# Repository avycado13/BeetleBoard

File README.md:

# BeetleBoard

Ever wanted to build a beetleweight but didn't want the huge mess of wires? No? Too bad. Meet BeetleBoard.
A perfect board for controlling your beetleweight battlebot using an ESP32.

## Features:
- 8 ports for ESCs
- 8 motor power ports
- Optional ExpressLRS Receiver
- 6 axis IMU with handling for up to 320Gs
- Software controllable battery undervoltage lockout circuitry
- Battery voltage sensing
- Powered by a XIAO ESP32-C6
- Ability to add a power switch (preferably fingertech)

## Why?
I built this because I saw battlebots at open sauce and thought "I want to make one of those". While looking through things about beetleweights and especially the ones with custom PCBs, I found out that most of the PCBs I found were specifically meant for one design and couldn't really be used for any type of bot. Coincidentally, My friend was trying to run a battlebots elective at our school and would need a control system to test before teaching the students.

## Bill of Materials (BOM)
**REVIEWERS PLEASE USE CSV**
This is just a rough list compiled from my schematic. The actual one is [here](./BOM.csv)

| Qty | Reference | Value | Package | Description |
|----:|-----------|-------|---------|-------------|
| 1 | U1 | XIAO ESP32-C6 SMD | XIAO | Seeed Studio XIAO ESP32-C6 module (main MCU) |
| 1 | U2 | TPS563200 | SOT-23-6 | 3A synchronous step-down buck converter (5V rail) |
| 1 | U3 | LSM6DSV320XTR | LGA-14 | 6-axis IMU, up to 320G |
| 1 | L1 | 4.7µH | 1210 | Buck converter power inductor |
| 5 | C1, C2, C3, C6, C8 | 22µF | 0805 | Bulk decoupling / output capacitance |
| 5 | C4, C5, C7, C9, C10 | 100nF | 0805 | Decoupling capacitors |
| 9 | R1-R6, R11-R13 | 33kΩ | 0805 | Resistor |
| 1 | R7 | 56kΩ | 0805 | Resistor |
| 1 | R8 | 10kΩ | 0805 | Resistor |
| 1 | R9 | 33.2kΩ | 0805 | Resistor |
| 1 | R10 | 120kΩ | 0805 | Resistor |
| 1 | R14 | 100kΩ | 0805 | Resistor |
| 1 | D1 | SMAJ40CA | SMA | 40V TVS diode (battery reverse/over-voltage protection) |
| 8 | D2-D9 | PESD5V0V1BA | SOD-323 | 5V ESD protection diodes |
| 1 | J1 | AMASS XT60-F | XT60 | Battery connector |
| 8 | J2-J7, J16, J17 | ESC signal port | 1×3 pin header 2.54mm | ESC signal power ports A-H |
| 8 | J8-J15 | VBAT ESC port | Solder wire 2-pin | Motor power ports |
| 1 | J18 | ELRS Receiver | BetaFPV Lite | Optional ExpressLRS receiver socket |
| 1 | SW1 | FingerTech Switch | Solder wire 2-pin | External power switch connection |
| 5 | TP1-TP5 | Test point | 3mm pad | Test/debug points (VBAT, 5V, GND, 3.3V, VBUS) |

# Firmware
At the moment, the firmware in the folder is some test code I had AI write. I will most definitely rewrite all the code when I have an actual board to test it on.

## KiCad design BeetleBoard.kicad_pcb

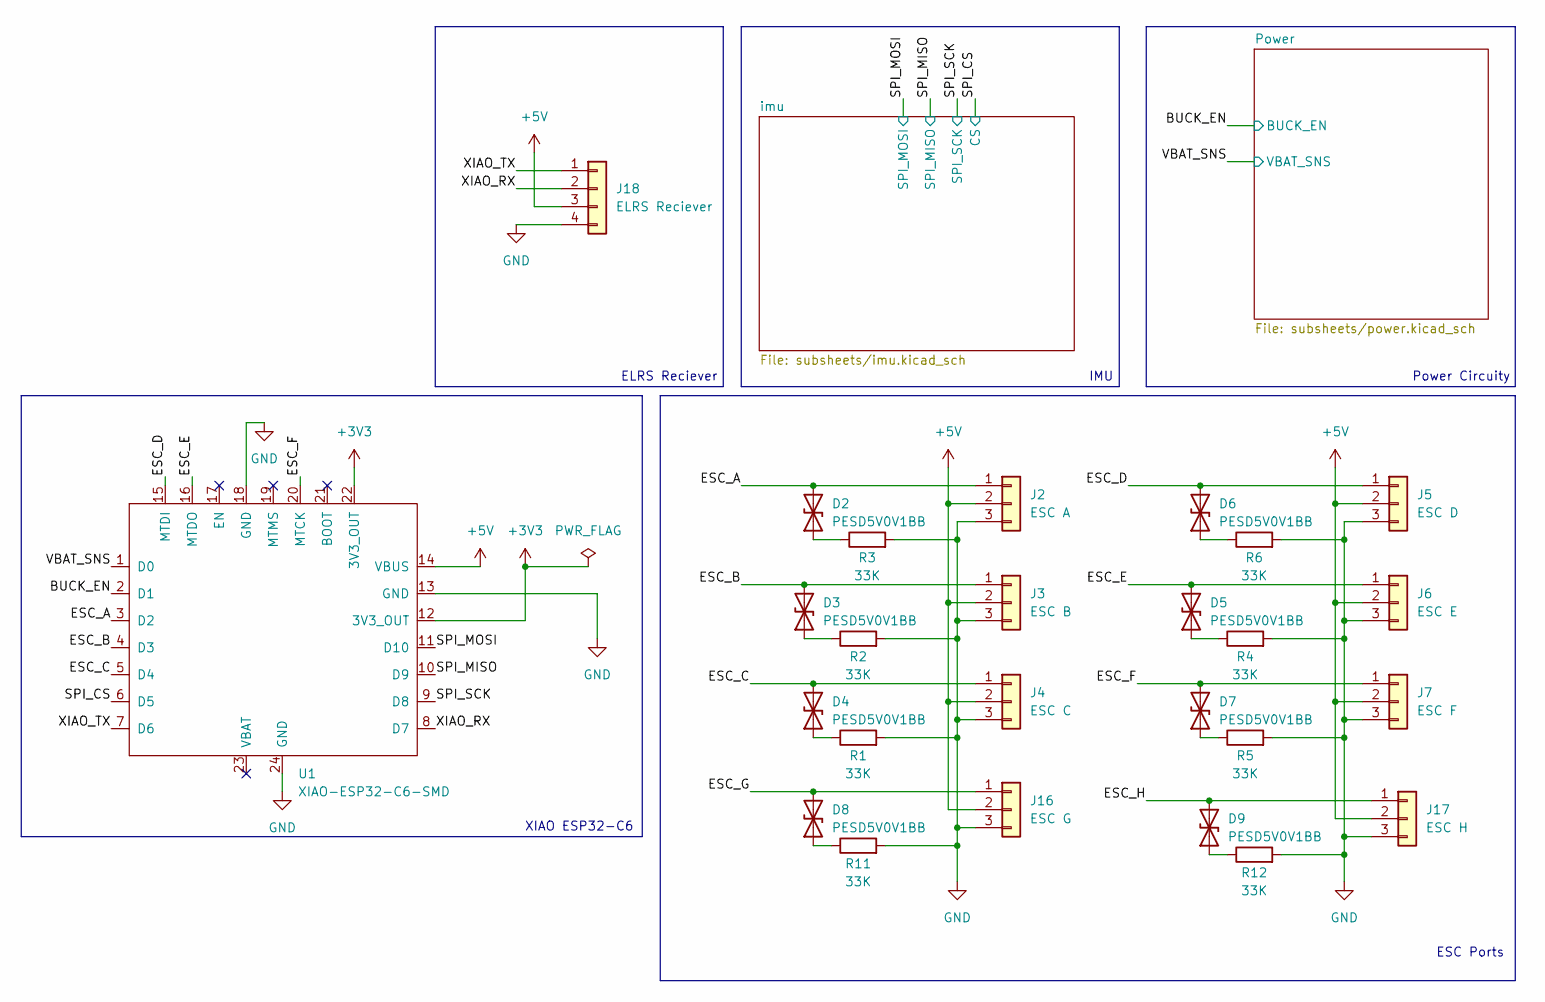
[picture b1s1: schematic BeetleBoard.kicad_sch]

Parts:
D2, D3, D4, D5, D6, D7, D8, D9: PESD5V0V1BB; D_SOD-323
J2: ESC A; PinHeader_1x03_P2.54mm_Vertical
J3: ESC B; PinHeader_1x03_P2.54mm_Vertical
J4: ESC C; PinHeader_1x03_P2.54mm_Vertical
J5: ESC D; PinHeader_1x03_P2.54mm_Vertical
J6: ESC E; PinHeader_1x03_P2.54mm_Vertical
J7: ESC F; PinHeader_1x03_P2.54mm_Vertical
J16: ESC G; PinHeader_1x03_P2.54mm_Vertical
J17: ESC H; PinHeader_1x03_P2.54mm_Vertical
J18: ELRS Reciever; BetaFPV_ELRS_Lite
R1, R2, R3, R4, R5, R6, R11, R12: 33K; R_0805_2012Metric_Pad1.20x1.40mm_HandSolder
U1: XIAO-ESP32-C6-SMD

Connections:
+3V3: U1.12 (3V3_OUT), U1.22 (3V3_OUT); also elsewhere on the board
+5V: J2.2 (+5V), J3.2 (+5V), J4.2 (+5V), J5.2 (+5V), J6.2 (+5V), J7.2 (+5V), J16.2 (+5V), J17.2 (+5V), J18.3, U1.14 (VBUS); also elsewhere on the board
/BUCK_EN: U1.2 (D1); also elsewhere on the board
/ESC_A: D2.2 (A2), J2.1 (DShot/PWM), U1.3 (D2)
/ESC_B: D3.2 (A2), J3.1 (DShot/PWM), U1.4 (D3)
/ESC_C: D4.2 (A2), J4.1 (DShot/PWM), U1.5 (D4)
/ESC_D: D6.2 (A2), J5.1 (DShot/PWM), U1.15 (MTDI)
/ESC_E: D5.2 (A2), J6.1 (DShot/PWM), U1.16 (MTDO)
/ESC_F: D7.2 (A2), J7.1 (DShot/PWM), U1.20 (MTCK)
/ESC_G: D8.2 (A2), J16.1 (DShot/PWM)
/ESC_H: D9.2 (A2), J17.1 (DShot/PWM)
/SPI_CS: U1.6 (D5); also elsewhere on the board
/SPI_MISO: U1.10 (D9); also elsewhere on the board
/SPI_MOSI: U1.11 (D10); also elsewhere on the board
/SPI_SCK: U1.9 (D8); also elsewhere on the board
/VBAT_SNS: U1.1 (D0); also elsewhere on the board
/XIAO_RX: J18.2, U1.8 (D7)
/XIAO_TX: J18.1, U1.7 (D6)
GND: J2.3 (GND), J3.3 (GND), J4.3 (GND), J5.3 (GND), J6.3 (GND), J7.3 (GND), J16.3 (GND), J17.3 (GND), J18.4, R1.2, R2.2, R3.2, R4.2, R5.2, R6.2, R11.2, R12.2, U1.13 (GND), U1.18 (GND), U1.24 (GND); also elsewhere on the board
unnamed: D2.1 (A1), R3.1
unnamed: D3.1 (A1), R2.1
unnamed: D4.1 (A1), R1.1
unnamed: D5.1 (A1), R4.1
unnamed: D6.1 (A1), R6.1
unnamed: D7.1 (A1), R5.1
unnamed: D8.1 (A1), R11.1
unnamed: D9.1 (A1), R12.1

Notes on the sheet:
Power Circuity
XIAO ESP32-C6
ELRS Reciever
IMU
ESC Ports

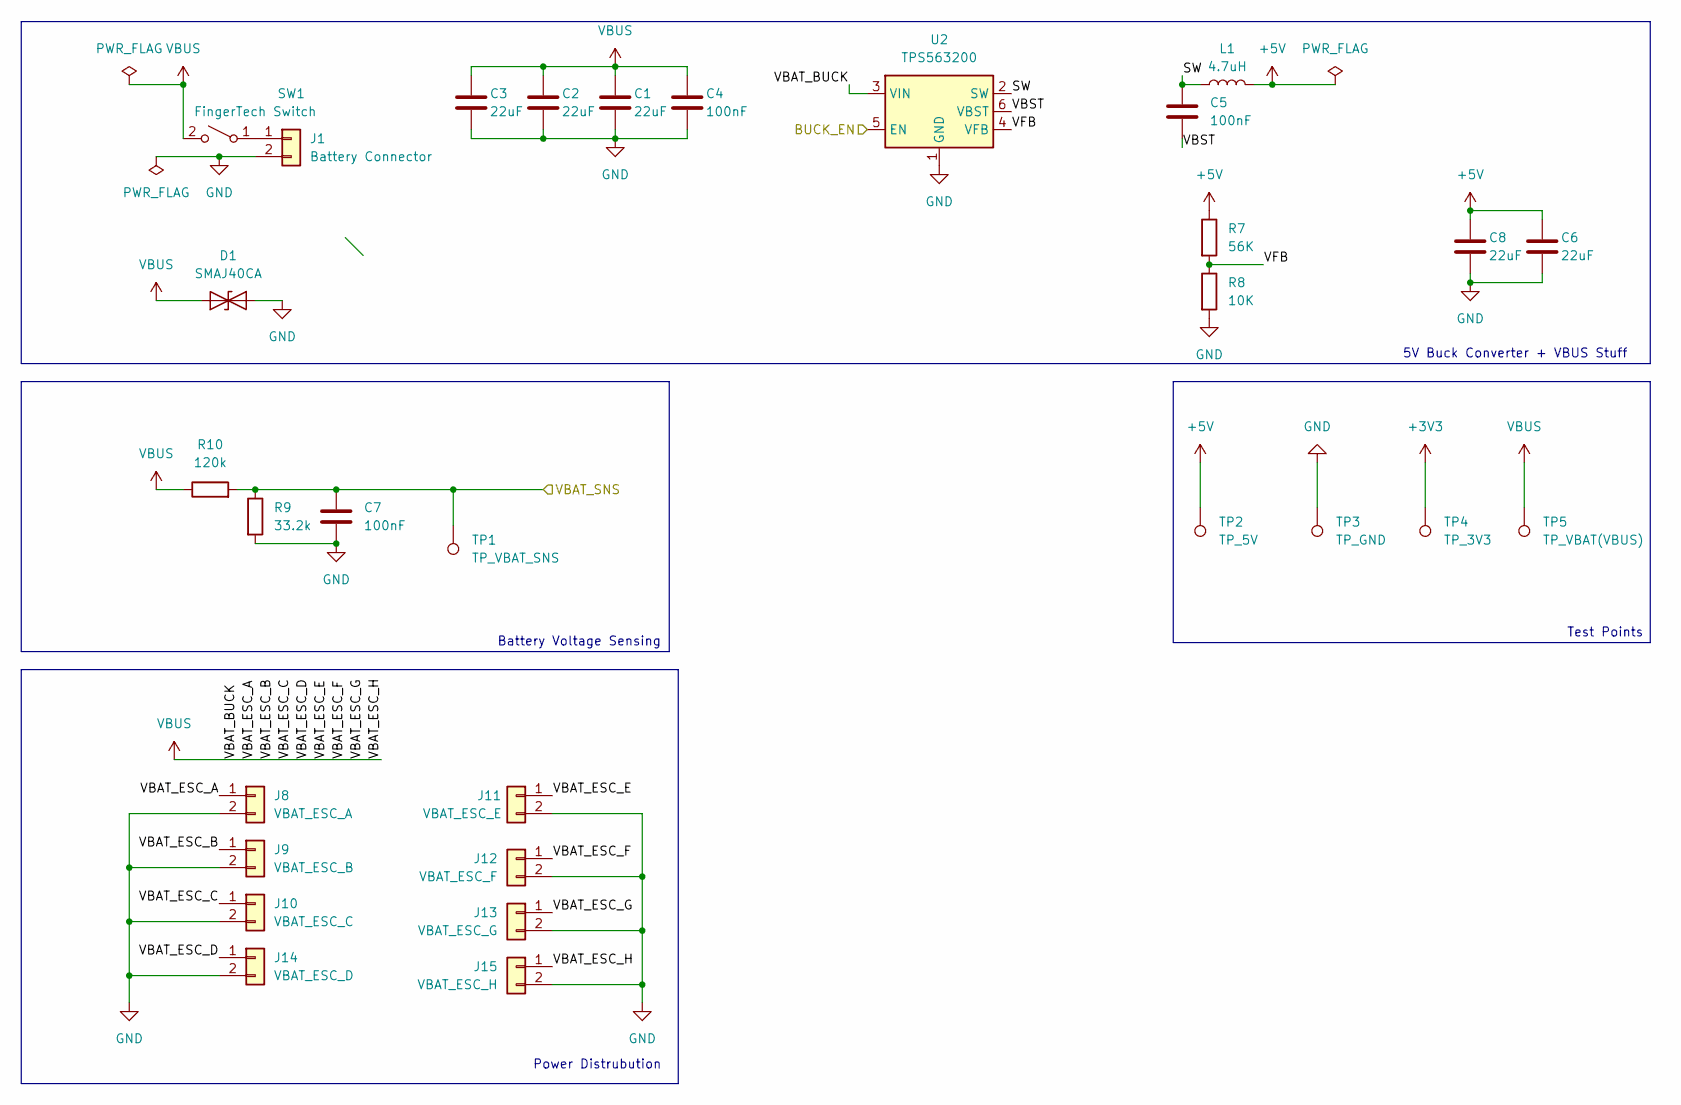
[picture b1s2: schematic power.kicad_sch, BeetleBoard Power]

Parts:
C1, C2, C3, C6, C8: 22uF; C_0805_2012Metric_Pad1.18x1.45mm_HandSolder
C4, C5, C7: 100nF; C_0805_2012Metric_Pad1.18x1.45mm_HandSolder
D1: SMAJ40CA; D_SMA
J1: Battery Connector; AMASS_XT60-F_1x02_P7.20mm_Vertical
J8: VBAT_ESC_A; Power_SolderPad_2Pin_P5.08mm_D2.0mm
J9: VBAT_ESC_B; Power_SolderPad_2Pin_P5.08mm_D2.0mm
J10: VBAT_ESC_C; Power_SolderPad_2Pin_P5.08mm_D2.0mm
J11: VBAT_ESC_E; Power_SolderPad_2Pin_P5.08mm_D2.0mm
J12: VBAT_ESC_F; Power_SolderPad_2Pin_P5.08mm_D2.0mm
J13: VBAT_ESC_G; Power_SolderPad_2Pin_P5.08mm_D2.0mm
J14: VBAT_ESC_D; Power_SolderPad_2Pin_P5.08mm_D2.0mm
J15: VBAT_ESC_H; Power_SolderPad_2Pin_P5.08mm_D2.0mm
L1: 4.7uH; L_1210_3225Metric_Pad1.42x2.65mm_HandSolder
R7: 56K; R_0805_2012Metric_Pad1.20x1.40mm_HandSolder
R8: 10K; R_0805_2012Metric_Pad1.20x1.40mm_HandSolder
R9: 33.2k; R_0805_2012Metric_Pad1.20x1.40mm_HandSolder
R10: 120k; R_0805_2012Metric_Pad1.20x1.40mm_HandSolder
SW1: FingerTech Switch; Power_SolderPad_2Pin_P5.08mm_D2.0mm
TP1: TP_VBAT_SNS; TestPoint_Pad_D3.0mm
TP2: TP_5V; TestPoint_Pad_D3.0mm
TP3: TP_GND; TestPoint_Pad_D3.0mm
TP4: TP_3V3; TestPoint_Pad_D3.0mm
TP5: TP_VBAT(VBUS); TestPoint_Pad_D3.0mm
U2: TPS563200; SOT-23-6

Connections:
+3V3: TP4.1 (1_1); also elsewhere on the board
+5V: C6.1, C8.1, L1.2, R7.1, TP2.1 (1_1); also elsewhere on the board
/BUCK_EN: U2.5 (EN); also elsewhere on the board
/Power/SW: C5.1, L1.1, U2.2 (SW)
/Power/VBST: C5.2, U2.6 (VBST)
/Power/VFB: R7.2, R8.1, U2.4 (VFB)
/VBAT_SNS: C7.1, R9.1, R10.2, TP1.1 (1_1); also elsewhere on the board
GND: C1.2, C2.2, C3.2, C4.2, C6.2, C7.2, C8.2, D1.2 (A2), J1.2, J8.2, J9.2, J10.2, J11.2, J12.2, J13.2, J14.2, J15.2, R8.2, R9.2, TP3.1 (1_1), U2.1 (GND); also elsewhere on the board
unnamed: J1.1, SW1.1 (A)
VBUS: C1.1, C2.1, C3.1, C4.1, D1.1 (A1), J8.1, J9.1, J10.1, J11.1, J12.1, J13.1, J14.1, J15.1, R10.1, SW1.2 (B), TP5.1 (1_1), U2.3 (VIN)

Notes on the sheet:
Battery Voltage Sensing
5V Buck Converter + VBUS Stuff
Test Points
Power Distrubution

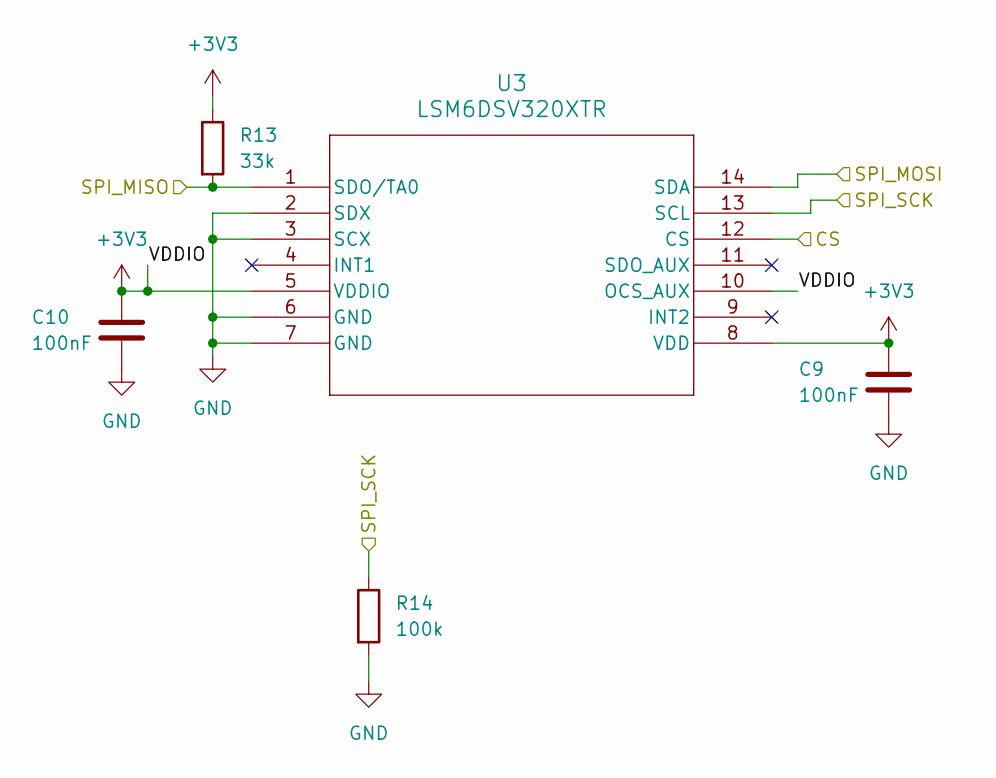
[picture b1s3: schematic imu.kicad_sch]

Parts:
C9, C10: 100nF; C_0805_2012Metric_Pad1.18x1.45mm_HandSolder
R13: 33k; R_0805_2012Metric_Pad1.20x1.40mm_HandSolder
R14: 100k; R_0805_2012Metric_Pad1.20x1.40mm_HandSolder
U3: LSM6DSV320XTR; LGA-14L_2p5X3X0p83_STM

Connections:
+3V3: C9.1, C10.1, R13.1, U3.5 (VDDIO), U3.8 (VDD), U3.10 (OCS_AUX); also elsewhere on the board
/SPI_CS: U3.12 (CS); also elsewhere on the board
/SPI_MISO: R13.2, U3.1 (SDO/TA0); also elsewhere on the board
/SPI_MOSI: U3.14 (SDA); also elsewhere on the board
/SPI_SCK: R14.1, U3.13 (SCL); also elsewhere on the board
GND: C9.2, C10.2, R14.2, U3.2 (SDX), U3.3 (SCX), U3.6 (GND), U3.7 (GND); also elsewhere on the board

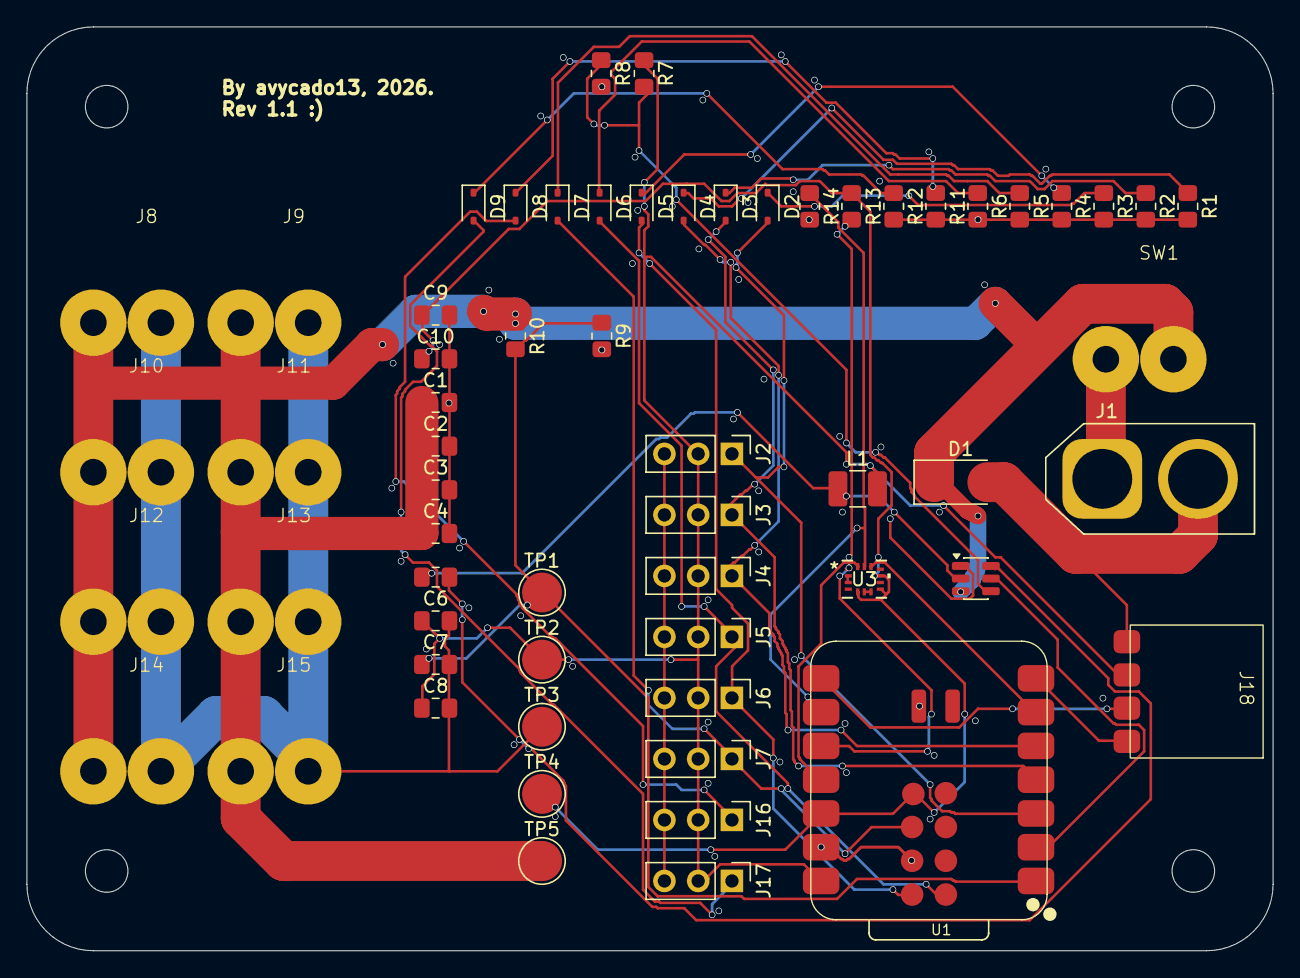
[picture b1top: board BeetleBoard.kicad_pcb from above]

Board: 2 copper layers, 93.8 x 69.5 mm, 61 parts (0 on the bottom side), 32 nets.

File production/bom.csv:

Designator,Footprint,Quantity,Value,LCSC Part #
"C1, C2, C3, C6, C8",0805,5,22uF,
"C10, C4, C5, C7, C9",0805,5,100nF,
D1,D_SMA,1,SMAJ40CA,
"D2, D3, D4, D5, D6, D7, D8, D9",D_SOD-323,8,PESD5V0V1BB,
J1,AMASS_XT60-F_1x02_P7.20mm_Vertical,1,Battery Connector,
J10,Power_SolderPad_2Pin_P5.08mm_D2.0mm,1,VBAT_ESC_C,
J11,Power_SolderPad_2Pin_P5.08mm_D2.0mm,1,VBAT_ESC_E,
J12,Power_SolderPad_2Pin_P5.08mm_D2.0mm,1,VBAT_ESC_F,
J13,Power_SolderPad_2Pin_P5.08mm_D2.0mm,1,VBAT_ESC_G,
J14,Power_SolderPad_2Pin_P5.08mm_D2.0mm,1,VBAT_ESC_D,
J15,Power_SolderPad_2Pin_P5.08mm_D2.0mm,1,VBAT_ESC_H,
J16,PinHeader_1x03_P2.54mm_Vertical,1,ESC G,
J17,PinHeader_1x03_P2.54mm_Vertical,1,ESC H,
J18,BetaFPV_ELRS_Lite,1,ELRS Reciever,
J2,PinHeader_1x03_P2.54mm_Vertical,1,ESC A,
J3,PinHeader_1x03_P2.54mm_Vertical,1,ESC B,
J4,PinHeader_1x03_P2.54mm_Vertical,1,ESC C,
J5,PinHeader_1x03_P2.54mm_Vertical,1,ESC D,
J6,PinHeader_1x03_P2.54mm_Vertical,1,ESC E,
J7,PinHeader_1x03_P2.54mm_Vertical,1,ESC F,
J8,Power_SolderPad_2Pin_P5.08mm_D2.0mm,1,VBAT_ESC_A,
J9,Power_SolderPad_2Pin_P5.08mm_D2.0mm,1,VBAT_ESC_B,
L1,1210,1,4.7uH,
"R1, R11, R12, R13, R2, R3, R4, R5, R6",0805,9,33K,
R10,0805,1,120k,
R14,0805,1,100k,
R7,0805,1,56K,
R8,0805,1,10K,
R9,0805,1,33.2k,
SW1,Power_SolderPad_2Pin_P5.08mm_D2.0mm,1,FingerTech Switch,
TP1,TestPoint_Pad_D3.0mm,1,TP_VBAT_SNS,
TP2,TestPoint_Pad_D3.0mm,1,TP_5V,
TP3,TestPoint_Pad_D3.0mm,1,TP_GND,
TP4,TestPoint_Pad_D3.0mm,1,TP_3V3,
TP5,TestPoint_Pad_D3.0mm,1,TP_VBAT(VBUS),
U1,XIAO-ESP32-C6-SMD,1,XIAO-ESP32-C6-SMD,
U2,SOT-23-6,1,TPS563200,
U3,LGA-14L_2p5X3X0p83_STM,1,LSM6DSV320XTR,

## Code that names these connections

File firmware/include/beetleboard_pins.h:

/**
 * @file beetleboard_pins.h
 * @brief Pin definitions and board hardware configuration for BeetleBoard
 * 
 * Hardware: Seeed Studio XIAO ESP32-C6 SMD module
 * Project:  BeetleBoard (Avycado13)
 * Target:   Beetleweight Battlebot Controller
 *
 * Generated from BeetleBoard KiCad Schematics:
 * - BeetleBoard.kicad_sch
 * - subsheets/power.kicad_sch
 * - subsheets/imu.kicad_sch
 */

#pragma once

#include <stdint.h>

// =============================================================================
// XIAO ESP32-C6 Onboard Peripherals
// =============================================================================
// The onboard user LED is active-LOW on GPIO 15
#define PIN_LED_BUILTIN         15
#define LED_ACTIVE_LEVEL        LOW
#define LED_INACTIVE_LEVEL      HIGH

// =============================================================================
// Power & Battery Monitoring Circuitry (subsheets/power.kicad_sch)
// =============================================================================
// VBAT Sensing: Voltage divider with R10 (120kΩ) and R9 (33.2kΩ), C7 (100nF) filter
// Connected to XIAO Pin D0 (ESP32-C6 GPIO 0 / ADC1_CH0)
#define PIN_VBAT_SNS            0

// Buck Converter Enable: Controls EN pin of TPS563200 3A 5V Buck Regulator (U2)
// Connected to XIAO Pin D1 (ESP32-C6 GPIO 1)
// Active-HIGH: Set HIGH to enable 5V rail; set LOW for software UVLO shutdown
#define PIN_BUCK_EN             1

// Resistor divider values for VBAT calculation:
// V_sns = V_bat * (R_BOTTOM / (R_TOP + R_BOTTOM))
// V_bat = V_sns * ((R_TOP + R_BOTTOM) / R_BOTTOM)
#define VBAT_DIVIDER_R_TOP      120000.0f   // 120 kΩ (R10)
#define VBAT_DIVIDER_R_BOTTOM   33200.0f    // 33.2 kΩ (R9)
#define VBAT_DIVIDER_RATIO      (VBAT_DIVIDER_R_BOTTOM / (VBAT_DIVIDER_R_TOP + VBAT_DIVIDER_R_BOTTOM)) // ~0.21671
#define VBAT_SCALE_FACTOR       ((VBAT_DIVIDER_R_TOP + VBAT_DIVIDER_R_BOTTOM) / VBAT_DIVIDER_R_BOTTOM) // ~4.61446

// =============================================================================
// ESC / Motor Signal Ports (BeetleBoard.kicad_sch)
// =============================================================================
// 6 ESC ports connected directly to ESP32-C6 GPIOs with ESD protection (D2-D7)
// and 33k pull-downs (R1-R6). Connectors are standard 3-pin 0.1" (Signal, 5V, GND).
#define NUM_ESC_CHANNELS        6

#define PIN_ESC_A               2    // J2: XIAO D2 (GPIO 2)
#define PIN_ESC_B               21   // J3: XIAO D3 (GPIO 21)
#define PIN_ESC_C               22   // J4: XIAO D4 (GPIO 22)
#define PIN_ESC_D               5    // J5: XIAO MTDI (GPIO 5)
#define PIN_ESC_E               7    // J6: XIAO MTDO (GPIO 7)
#define PIN_ESC_F               6    // J7: XIAO MTCK (GPIO 6)

// Note: Ports ESC_G (J16) and ESC_H (J17) exist on the PCB with ESD protection
// and pull-downs, but their signal pins are unrouted to the MCU on this revision.
#define PIN_ESC_G_CONNECTED     0
#define PIN_ESC_H_CONNECTED     0

// Array of active ESC pins for easy iteration
static const uint8_t ESC_PINS[NUM_ESC_CHANNELS] = {
    PIN_ESC_A,  // Channel 0 (ESC A)
    PIN_ESC_B,  // Channel 1 (ESC B)
    PIN_ESC_C,  // Channel 2 (ESC C)
    PIN_ESC_D,  // Channel 3 (ESC D)
    PIN_ESC_E,  // Channel 4 (ESC E)
    PIN_ESC_F   // Channel 5 (ESC F)
};

// =============================================================================
// 6-Axis High-G IMU: LSM6DSV320XTR (subsheets/imu.kicad_sch)
// =============================================================================
// Communicates over dedicated 4-wire SPI bus (3.3V logic)
#define PIN_IMU_CS              23   // U3 Pin 12: XIAO D5 (GPIO 23)
#define PIN_IMU_SCK             19   // U3 Pin 13: XIAO D8 (GPIO 19, R14 100k pulldown)
#define PIN_IMU_MISO            20   // U3 Pin 1:  XIAO D9 (GPIO 20, R13 33k pullup)
#define PIN_IMU_MOSI            18   // U3 Pin 14: XIAO D10 (GPIO 18)

// LSM6DSV320X Device ID & SPI Speeds
#define LSM6DSV320X_WHO_AM_I_VAL 0x73
#define IMU_SPI_CLOCK_HZ        4000000 // 4 MHz SPI clock

// =============================================================================
// ExpressLRS (ELRS) / CRSF Receiver Port (BeetleBoard.kicad_sch)
// =============================================================================
// J18: 4-pin header for BetaFPV Lite / ExpressLRS receivers (TX, RX, 5V, GND)
#define PIN_ELRS_TX             16   // J18 Pin 1: XIAO D6 (GPIO 16) -> Receiver RX
#define PIN_ELRS_RX             17   // J18 Pin 2: XIAO D7 (GPIO 17) <- Receiver TX
#define ELRS_CRSF_BAUDRATE      420000  // Standard CRSF baud rate
#define ELRS_SERIAL_PORT        Serial1

// =============================================================================
// Safety & Battery Cutoff Defaults
// =============================================================================
#define LIPO_CELL_MIN_VOLTAGE   3.30f   // Cutoff threshold per cell (V)
#define LIPO_CELL_WARN_VOLTAGE  3.50f   // Warning threshold per cell (V)
#define LIPO_CELL_MAX_VOLTAGE   4.25f   // Overvoltage detection threshold per cell (V)
#define UVLO_HYSTERESIS_VOLTAGE 0.50f   // Voltage rise needed before re-enabling buck

// Default PWM timings (standard 50 Hz RC PWM, in microseconds)
#define PWM_FREQUENCY_HZ        50
#define PWM_PULSE_MIN_US        1000    // Full reverse / minimum throttle
#define PWM_PULSE_NEUTRAL_US    1500    // Neutral / stop for bidirectional ESCs
#define PWM_PULSE_MAX_US        2000    // Full forward / maximum throttle
#define PWM_DISARM_US           1000    // Disarmed / safe pulse
